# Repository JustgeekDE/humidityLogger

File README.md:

A basic humidity / temprature logger system using a DHT11 sensor with a ESP8266 controller.

Backend
=======
In the backend folder you can find the nodeJS app to store the sensor data

To automatically setup the backend on an raspberry pi, you can use ansible:

    ansible-playbook -i hosts basic-setup.yml --ask-pass

Sensor
======
In `sensor/src/` you can find the lua scripts for the ESP8266. You will need a NodeMCU build with the `cjson, http, file` and `DHT` modules enabled.    
After loading the src code onto the ESP module execute 

    require("config").setValue("wifiSSID", "YOUR NETWORK NAME") 
    require("config").setValue("wifiPass", "YOUR NETWORK PASS") 
    require("config").setValue("sensorId", "YOUR SENSOR ID") 
    require("config").setValue("logEndpoint", "URL OF NODE APP") 

in the interactive shell, to set the necessary configuration values.

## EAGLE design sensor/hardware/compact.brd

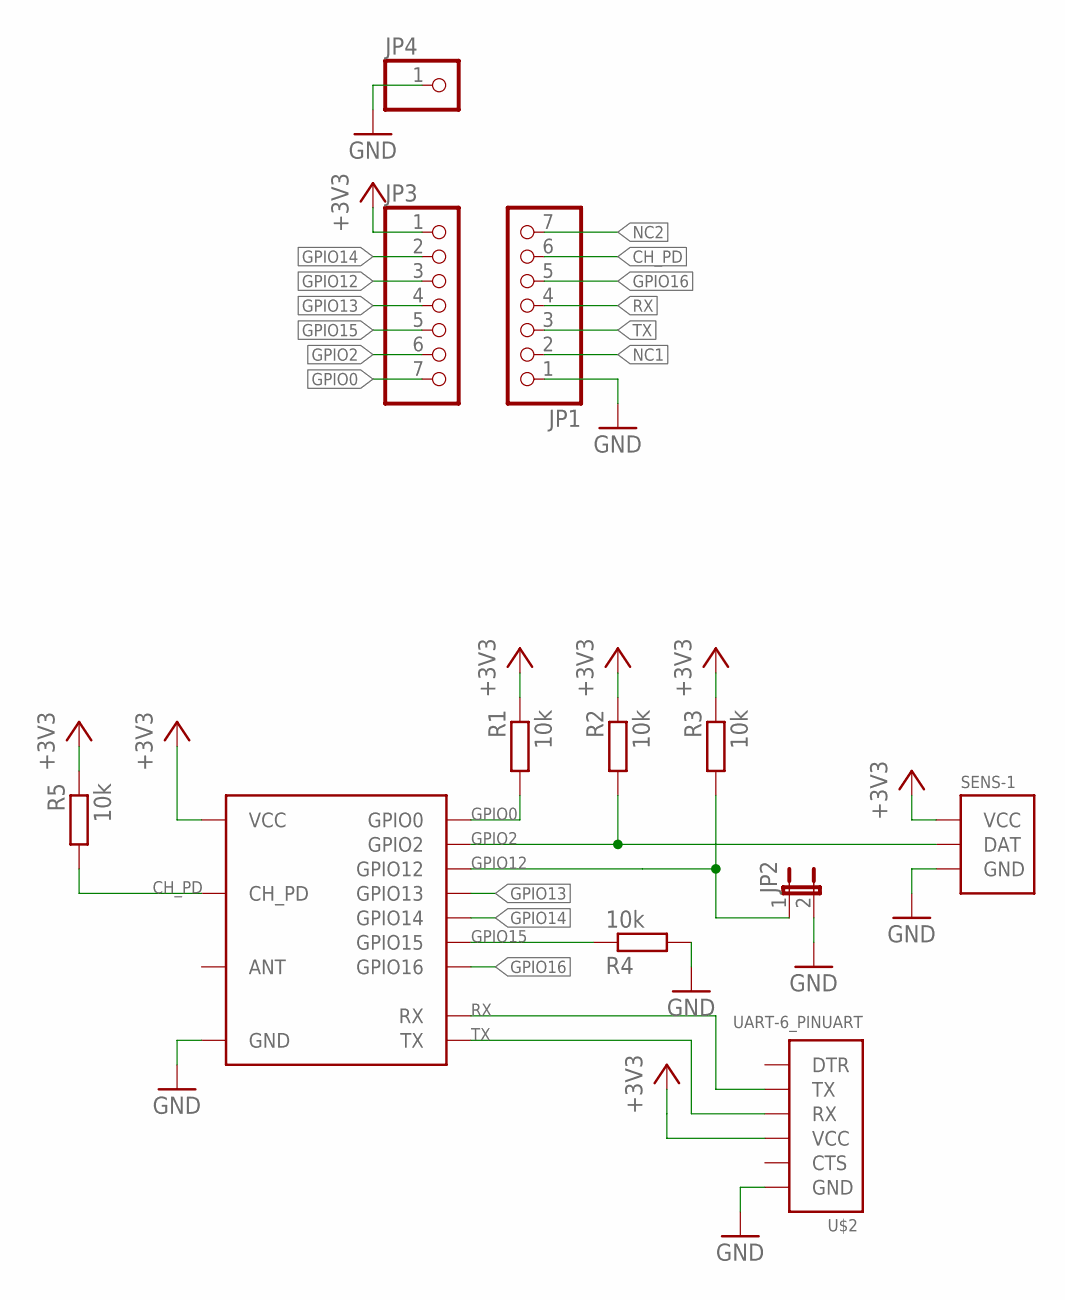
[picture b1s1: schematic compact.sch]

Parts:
JP1, JP3: PINHD-1X7; 1X07
JP2: JP1E; JP1
JP4: PINHD-1X1; 1X01
R1, R2, R3, R4, R5: 10k; R0603
SENS-1: DHT11DHT11; SENSOR-DHT11
U$1: ESP8266-03; ESP8266-ESP-03
U$2: UART-6_PINUART; ANGLE-1X6

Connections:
+3V3: JP3.1, R1.1, R2.1, R3.1, R5.1, SENS-1.P$1 (VCC), U$1.P$8 (VCC), U$2.3 (VCC)
CH_PD: JP1.6, R5.2, U$1.P$6 (CH_PD)
GND: JP1.1, JP2.2, JP4.1, R4.2, SENS-1.P$4 (GND), U$1.P$1 (GND), U$2.1 (GND)
GPIO0: JP3.7, R1.2, U$1.P$14 (GPIO0)
GPIO2: JP3.6, R2.2, SENS-1.P$2 (DAT), U$1.P$13 (GPIO2)
GPIO12: JP2.1, JP3.3, R3.2, U$1.P$10 (GPIO12)
GPIO13: JP3.4, U$1.P$11 (GPIO13)
GPIO14: JP3.2, U$1.P$9 (GPIO14)
GPIO15: JP3.5, R4.1, U$1.P$12 (GPIO15)
GPIO16: JP1.5, U$1.P$5 (GPIO16)
NC1: JP1.2
NC2: JP1.7
RX: JP1.4, U$1.P$4 (RX), U$2.5 (TX)
TX: JP1.3, U$1.P$3 (TX), U$2.4 (RX)

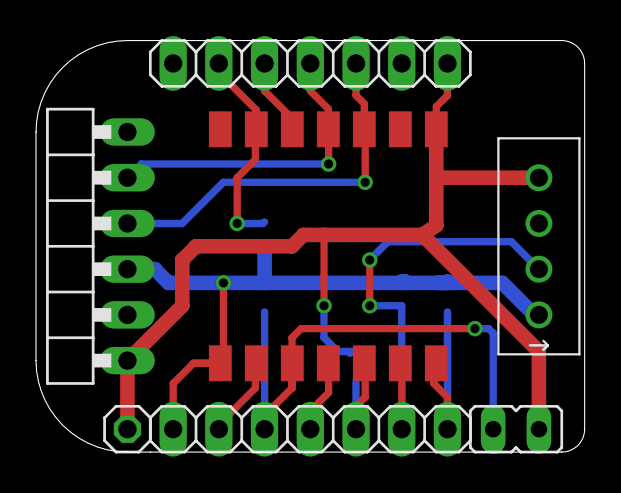
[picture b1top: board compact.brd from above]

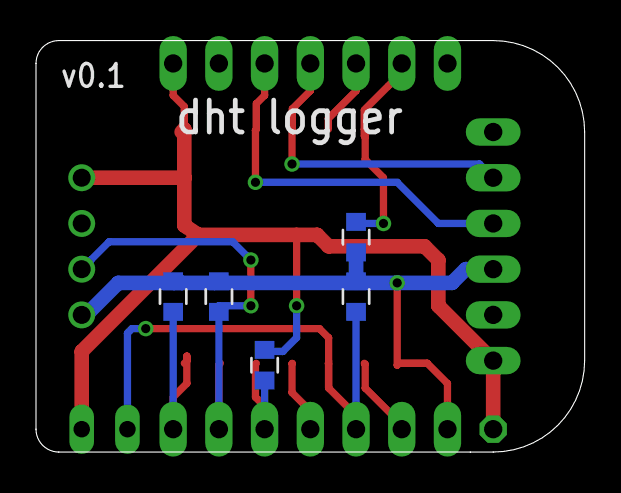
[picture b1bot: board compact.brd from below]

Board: 2 copper layers, 30.5 x 22.9 mm, 13 parts (5 on the bottom side), 12 nets.

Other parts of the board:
U$3: LOGO-JUSTGEEK-XXXS-MASK

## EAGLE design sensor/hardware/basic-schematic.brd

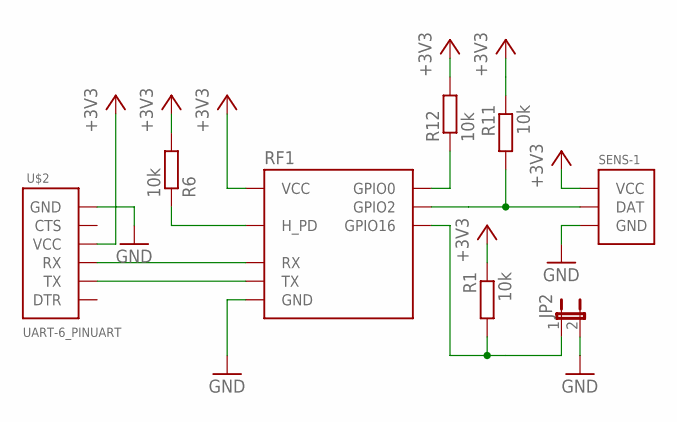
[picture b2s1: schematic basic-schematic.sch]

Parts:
JP2: JP1E; JP1
R1, R6, R11, R12: 10k; 0207/7
RF1: ESP2866-ESP-01THT; ESP8266-ESP-01
SENS-1: DHT11DHT11; SENSOR-DHT11
U$2: UART-6_PINUART; ANGLE-1X6

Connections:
+3V3: R1.1, R6.2, R11.1, R12.2, RF1.VCC, SENS-1.P$1 (VCC), U$2.3 (VCC)
GND: JP2.2, RF1.GND, SENS-1.P$4 (GND), U$2.1 (GND)
IO0: R12.1, RF1.GPIO0
IO2: R11.2, RF1.GPIO2, SENS-1.P$2 (DAT)
IO16: JP2.1, R1.2, RF1.GPIO16
RESET: R6.1, RF1.H_PD
RX: RF1.RX, U$2.4 (RX)
TX: RF1.TX, U$2.5 (TX)

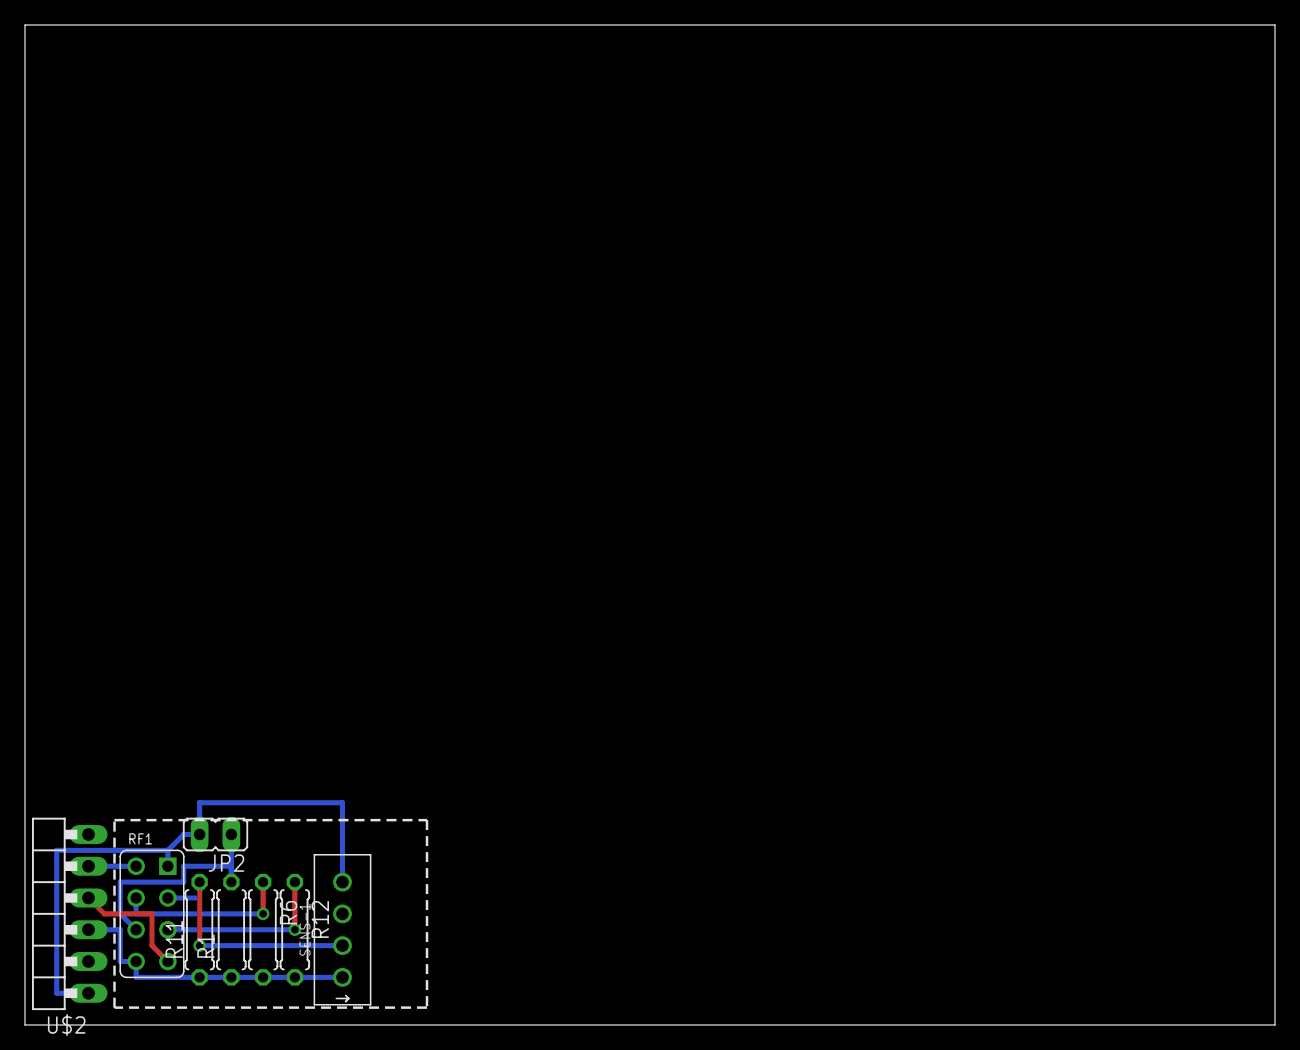
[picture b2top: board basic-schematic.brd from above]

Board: 2 copper layers, 100.0 x 80.0 mm, 8 parts (0 on the bottom side), 8 nets.

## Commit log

2016-03-12 ignoring lua, node and eagle files
2016-03-12 initial backend to store data
2016-03-12 added some log output
2016-03-12 basic sensor firmware
2016-03-12 Adjusted update intervall to 1 minute
2016-03-12 moved database to file instead of memory
2016-03-12 removed output
2016-03-12 Added ansible setup files
2016-03-12 Typo in apt source
2016-03-12 added node version from tarball
2016-03-12 fixed indentation of yaml
2016-03-12 Added repo to package json
2016-03-12 Added starting the backend
2016-03-13 Added hardware examples
2016-03-13 Added new smd version
2016-03-13 added start script for pi
2016-03-13 Trying out service to start app
2016-03-13 made backend executable
2016-03-13 And now with the correct shebang
2016-03-13 Ignoring databases
2016-03-13 more service fixing
2016-03-13 Looks like p2m is the best option for automatically starting the backend
2016-03-13 added readme
